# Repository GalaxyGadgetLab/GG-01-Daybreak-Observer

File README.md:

# 銀河ガジェット1号：黎明の観測者(Daybreak Observer)

>共に夜明けと新時代の幕開けを観測しようじゃないかッ!

## 概要
スピーカを搭載した親機を枕元に，停止用RFIDリーダを備えた子機をリビングに設置します．
アラーム時刻の設定は，同一ネットワーク内のデバイスからブラウザ経由で親機のWebサーバーへアクセスして行います．
リビングまで移動してラボの会員証(RFIDタグ)をかざさない限り，アラームは止まりません．

## 構成
## ハードウェア

### 親機(Parent Unit)
| Function | Component / Module | Interface |
| :--- | :--- | :--- |
| MCU | ESP32-WROOM-32E | - |
| Audio | DFPlayer Mini | UART |
| RTC | DS3231  | I2C |
| Display | 2.8"TFT(ILI9341) | SPI |

### 子機(Child Unit)
| Function | Component / Module | Interface |
| :--- | :--- | :--- |
| MCU | ESP32-WROOM-32E | - |
| RFID | MFRC522 (NFC Reader/Writer) | SPI |
| Indicator | High-brightness Red LED | GPIO |
| Alarm | Piezoelectric Buzzer | GPIO |

## PCB設計
本プロジェクトでは，専用のカスタム基板を設計・製作しました．
- **Design Tool：** KiCad 9.0
- **Layer:** 2 Layers

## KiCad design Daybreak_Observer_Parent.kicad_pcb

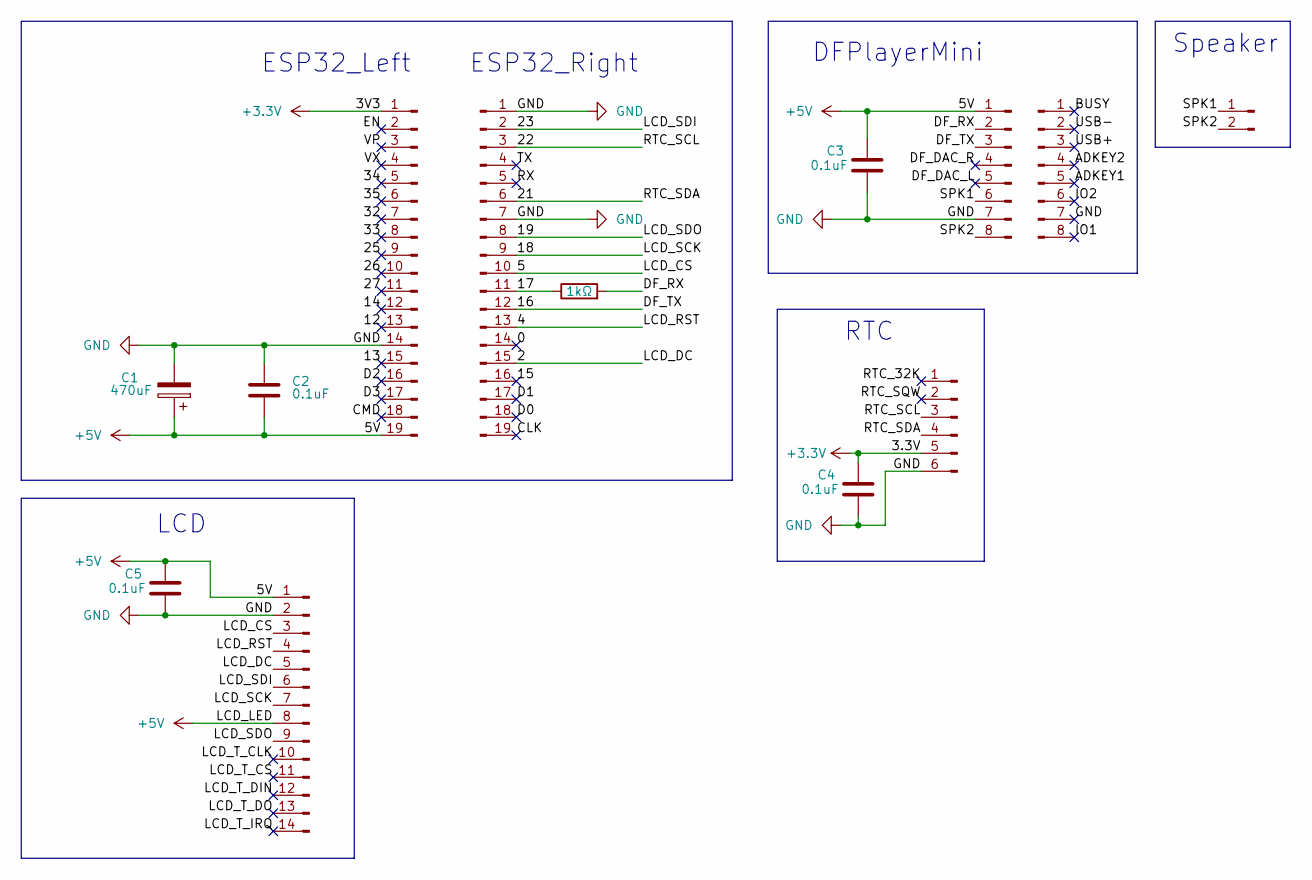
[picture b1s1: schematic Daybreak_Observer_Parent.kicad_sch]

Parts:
C1: 470uF; CP_Radial_D6.3mm_P2.50mm
C2, C3, C4, C5: 0.1uF; C_Disc_D5.0mm_W2.5mm_P2.50mm
J1, J2: Conn_01x19_Pin; PinSocket_1x19_P2.54mm_Vertical
J3, J4: Conn_01x08_Pin; PinSocket_1x08_P2.54mm_Vertical
J5: Conn_01x06_Pin; PinSocket_1x06_P2.54mm_Vertical
J6: Conn_01x14_Pin; PinSocket_1x14_P2.54mm_Vertical
J7: Conn_01x02_Pin; JST_PH_B2B-PH-K_1x02_P2.00mm_Vertical
R1: 1kΩ; R_Axial_DIN0207_L6.3mm_D2.5mm_P7.62mm_Horizontal

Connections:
+3.3V: C4.1, J1.1, J5.5
+5V: C1.1, C2.2, C3.1, C5.1, J1.19, J3.1, J6.1, J6.8
/0: J2.14
/2: J2.15, J6.5
/4: J2.13, J6.4
/5: J2.10, J6.3
/12: J1.13
/13: J1.15
/14: J1.12
/15: J2.16
/16: J2.12, J3.3
/17: J2.11, R1.1
/18: J2.9, J6.7
/19: J2.8, J6.9
/21: J2.6, J5.4
/22: J2.3, J5.3
/23: J2.2, J6.6
/25: J1.9
/26: J1.10
/27: J1.11
/32: J1.7
/33: J1.8
/34: J1.5
/35: J1.6
/ADKEY1: J4.5
/ADKEY2: J4.4
/BUSY: J4.1
/CLK: J2.19
/CMD: J1.18
/D0: J2.18
/D1: J2.17
/D2: J1.16
/D3: J1.17
/DF_DAC_L: J3.5
/DF_DAC_R: J3.4
/DF_RX: J3.2, R1.2
/EN: J1.2
/IO1: J4.8
/IO2: J4.6
/LCD_T_CLK: J6.10
/LCD_T_CS: J6.11
/LCD_T_DIN: J6.12
/LCD_T_DO: J6.13
/LCD_T_IRQ: J6.14
/RTC_32K: J5.1
/RTC_SQW: J5.2
/RX: J2.5
/SPK1: J3.6, J7.1
/SPK2: J3.8, J7.2
/TX: J2.4
/USB+: J4.3
/USB-: J4.2
/VP: J1.3
/VX: J1.4
GND: C1.2, C2.1, C3.2, C4.2, C5.2, J1.14, J2.1, J2.7, J3.7, J4.7, J5.6, J6.2

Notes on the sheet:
LCD
ESP32_Left
Speaker
RTC
ESP32_Right
DFPlayerMini

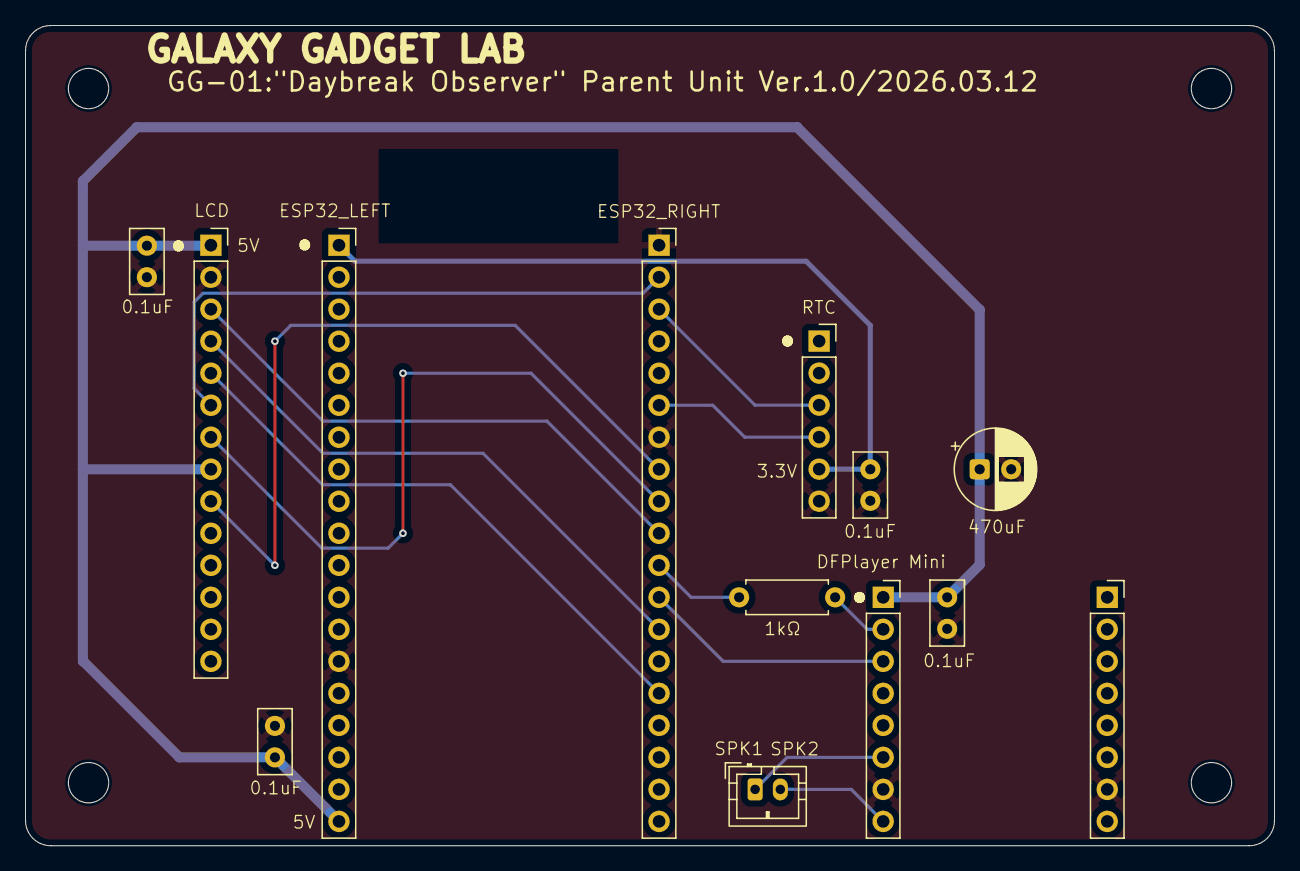
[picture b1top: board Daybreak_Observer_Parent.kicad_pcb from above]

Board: 2 copper layers, 99.1 x 65.1 mm, 13 parts (0 on the bottom side), 16 nets.

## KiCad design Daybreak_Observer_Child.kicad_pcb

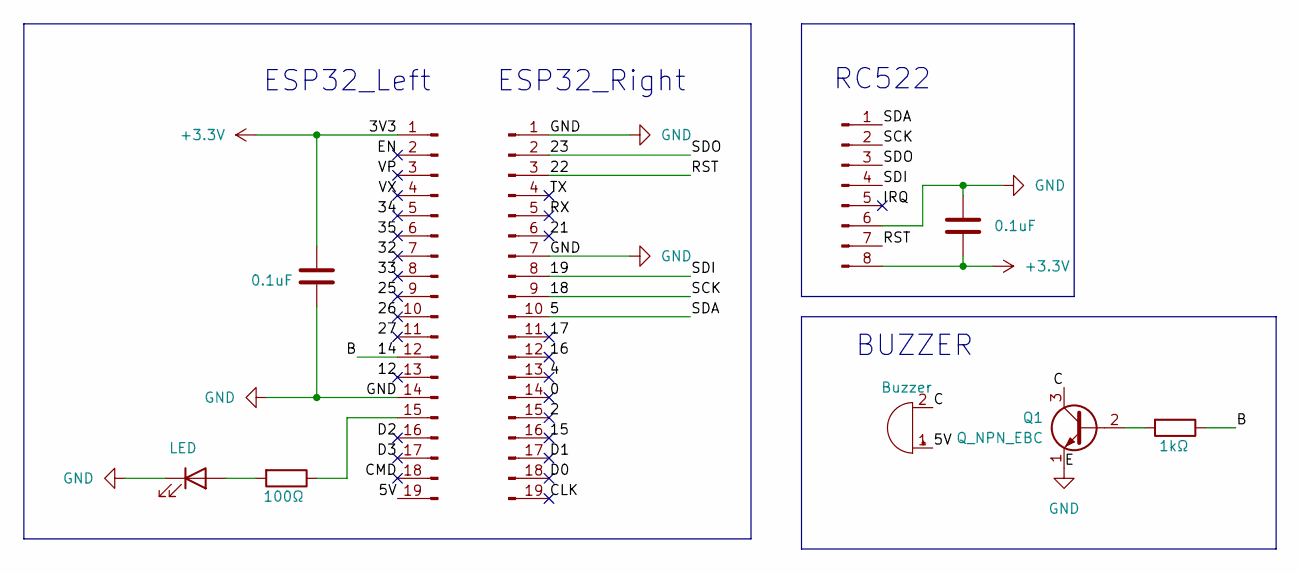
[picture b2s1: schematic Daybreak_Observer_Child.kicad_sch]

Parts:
BZ1: Buzzer; Buzzer_12x9.5RM7.6
C1, C2: 0.1uF; C_Disc_D5.0mm_W2.5mm_P2.50mm
D1: LED; LED_D3.0mm
J1, J2: Conn_01x19_Pin; PinSocket_1x19_P2.54mm_Vertical
J3: Conn_01x08_Pin; PinSocket_1x08_P2.54mm_Vertical
Q1: Q_NPN_EBC; TO-92_Inline
R2: 100Ω; R_Axial_DIN0207_L6.3mm_D2.5mm_P7.62mm_Horizontal
R3: 1kΩ; R_Axial_DIN0207_L6.3mm_D2.5mm_P7.62mm_Horizontal

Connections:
+3.3V: C1.1, C2.2, J1.1, J3.8
/0: J2.14
/2: J2.15
/4: J2.13
/5: J2.10, J3.1
/5V: BZ1.1 (+), J1.19
/12: J1.13
/14: J1.12, R3.1
/15: J2.16
/16: J2.12
/17: J2.11
/18: J2.9, J3.2
/19: J2.8, J3.4
/21: J2.6
/22: J2.3, J3.7
/23: J2.2, J3.3
/25: J1.9
/26: J1.10
/27: J1.11
/32: J1.7
/33: J1.8
/34: J1.5
/35: J1.6
/C: BZ1.2 (-), Q1.3 (C)
/CLK: J2.19
/CMD: J1.18
/D0: J2.18
/D1: J2.17
/D2: J1.16
/D3: J1.17
/EN: J1.2
/IRQ: J3.5
/RX: J2.5
/TX: J2.4
/VP: J1.3
/VX: J1.4
GND: C1.2, C2.1, D1.1 (K), J1.14, J2.1, J2.7, J3.6, Q1.1 (E)
unnamed: D1.2 (A), R2.2
unnamed: J1.15, R2.1
unnamed: Q1.2 (B), R3.2

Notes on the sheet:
RC522
BUZZER
ESP32_Left
ESP32_Right

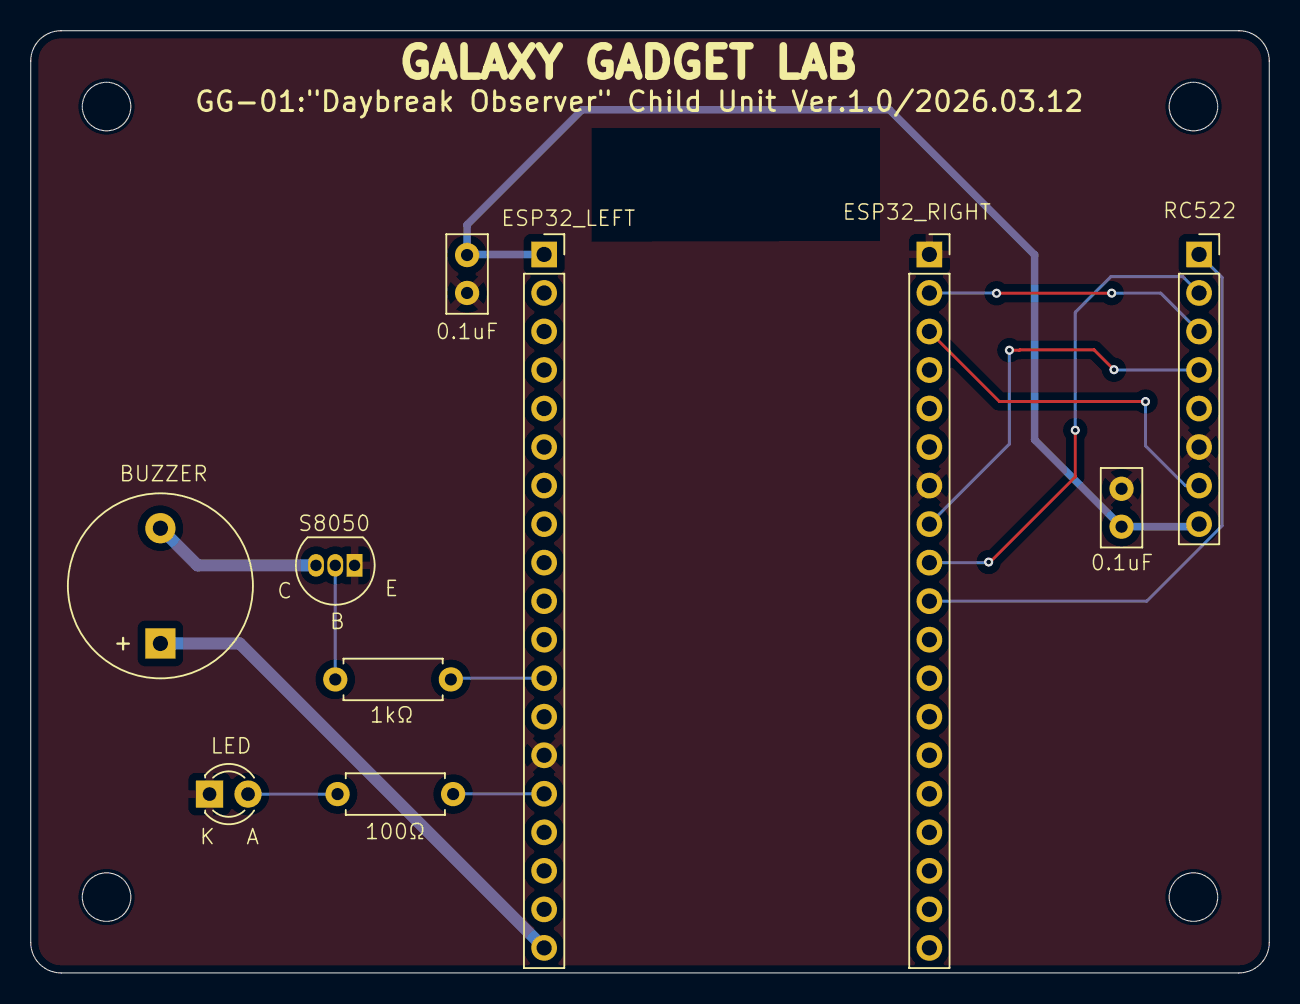
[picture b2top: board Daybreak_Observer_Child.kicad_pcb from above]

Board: 2 copper layers, 81.7 x 62.1 mm, 10 parts (0 on the bottom side), 13 nets.

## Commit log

2026-03-14 Add KiCad v9.0 hardware design
2026-03-14 Rename Daybreak_Observer_Parent.ino to Parent_Unit/Daybreak_Observer_Parent.ino
2026-03-14 Rename Daybreak_Observer_Parent.kicad_pcb to Parent_Unit/Daybreak_Observer_Parent.kicad_pcb
2026-03-14 Rename Daybreak_Observer_Parent.kicad_pro to Parent_Unit/Daybreak_Observer_Parent.kicad_pro
2026-03-14 Rename Daybreak_Observer_Parent.kicad_sch to Parent_Unit/Daybreak_Observer_Parent.kicad_sch
2026-03-14 Rename Daybreak_Observer_Child.ino to Child_Unit/Daybreak_Observer_Child.ino
2026-03-14 Rename Daybreak_Observer_Child.kicad_pcb to Child_Unit/Daybreak_Observer_Child.kicad_pcb
2026-03-14 Rename Daybreak_Observer_Child.kicad_pro to Child_Unit/Daybreak_Observer_Child.kicad_pro
2026-03-14 Rename Daybreak_Observer_Child.kicad_sch to Child_Unit/Daybreak_Observer_Child.kicad_sch
